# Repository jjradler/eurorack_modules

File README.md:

View this project on [CADLAB.io](https://cadlab.io/project/2451). 

# eurorack_modules

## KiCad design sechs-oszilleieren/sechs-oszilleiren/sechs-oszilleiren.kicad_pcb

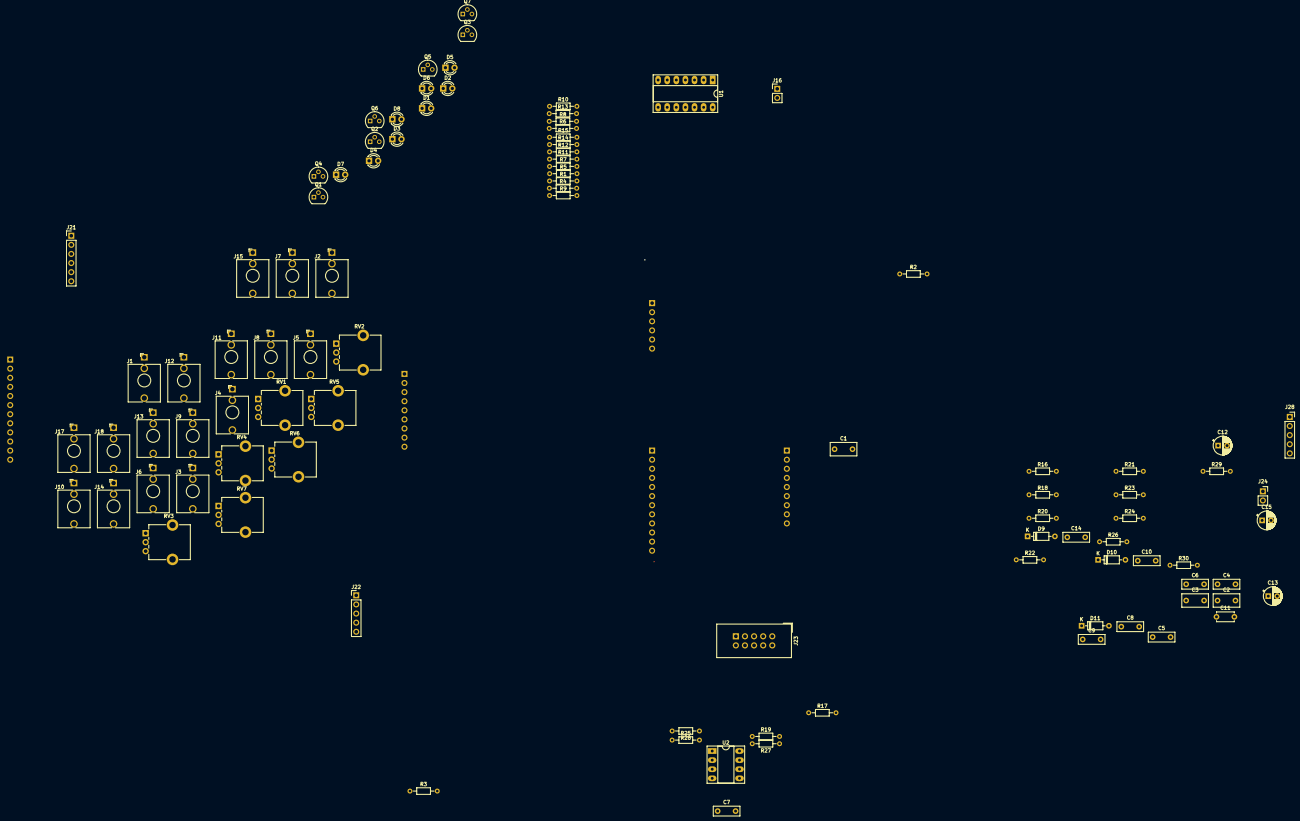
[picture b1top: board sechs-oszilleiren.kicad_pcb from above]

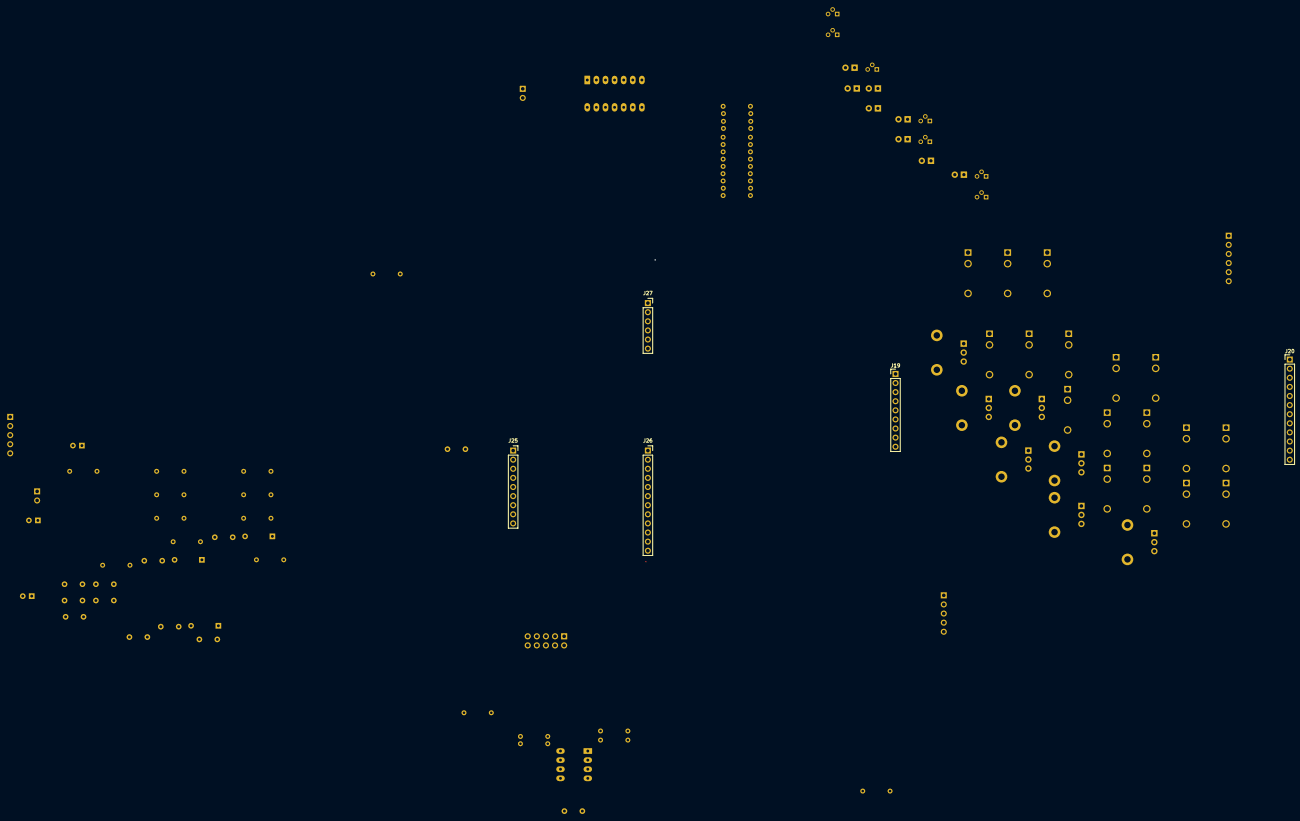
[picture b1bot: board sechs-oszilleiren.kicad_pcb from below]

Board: 2 copper layers, 100 parts (5 on the bottom side), 82 nets.

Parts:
C1, C2, C3: 1.0uF; C_Rect_L7.2mm_W3.5mm_P5.00mm_FKS2_FKP2_MKS2_MKP2
C4, C5, C6, C7, C8, C9: 0.1uF; C_Rect_L7.2mm_W2.5mm_P5.00mm_FKS2_FKP2_MKS2_MKP2
C10: 47pF; C_Rect_L7.2mm_W2.5mm_P5.00mm_FKS2_FKP2_MKS2_MKP2
C11: 27pF; C_Disc_D4.7mm_W2.5mm_P5.00mm
C12, C13, C15: 10uF; CP_Radial_D5.0mm_P2.50mm
C14: 0.01uF; C_Rect_L7.2mm_W2.5mm_P5.00mm_FKS2_FKP2_MKS2_MKP2
D1, D2, D3, D4, D5, D6, D7: R; LED_D3.0mm
D8: Y; LED_D3.0mm
D9, D10, D11: 1N4148; D_DO-35_SOD27_P7.62mm_Horizontal
J1, J2, J3, J4, J5, J6, J7, J8, J9, J10, J11, J12, J13, J14, J15, J17, J18: AudioJack2; Jack_3.5mm_QingPu_WQP-PJ398SM_Vertical_CircularHoles
J16: Conn_01x02_Male; PinHeader_1x02_P2.54mm_Vertical
J19: Conn_01x09_Male; PinHeader_1x09_P2.54mm_Vertical
J20: Conn_01x12_Male; PinHeader_1x12_P2.54mm_Vertical
J21: Conn_01x06_Male; PinHeader_1x06_P2.54mm_Vertical
J22: Conn_01x05_Male; PinHeader_1x05_P2.54mm_Vertical
J23: Conn_IDC_Box_Header_02x05_Top_Bottom; IDC-Header_2x05_Pitch2.54mm_Straight
J24: Conn_01x02_Female; PinSocket_1x02_P2.54mm_Vertical
J25: Conn_01x09_Female; PinSocket_1x09_P2.54mm_Vertical
J26: Conn_01x12_Female; PinSocket_1x12_P2.54mm_Vertical
J27: Conn_01x06_Female; PinSocket_1x06_P2.54mm_Vertical
J28: Conn_01x05_Female; PinSocket_1x05_P2.54mm_Vertical
Q1, Q2, Q3, Q4, Q5, Q6, Q7: 2N3904; TO-92
R1, R2, R3, R7, R8, R9, R14, R28: 47K; R_Axial_DIN0204_L3.6mm_D1.6mm_P7.62mm_Horizontal
R4, R5, R6, R10, R11, R12, R15: 2K; R_Axial_DIN0204_L3.6mm_D1.6mm_P7.62mm_Horizontal
R13: 22K; R_Axial_DIN0204_L3.6mm_D1.6mm_P7.62mm_Horizontal
R16, R17, R18: 1K; R_Axial_DIN0204_L3.6mm_D1.6mm_P7.62mm_Horizontal
R19, R20, R21, R22, R23, R24, R25, R26, R27: 10K; R_Axial_DIN0204_L3.6mm_D1.6mm_P7.62mm_Horizontal
R29, R30: 100R; R_Axial_DIN0204_L3.6mm_D1.6mm_P7.62mm_Horizontal
RV1, RV2, RV3, RV4, RV5, RV6: B100K; Potentiometer_Alpha_RD901F-40-00D_Single_Vertical_CircularH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
RV7: A10K; Potentiometer_Alpha_RD901F-40-00D_Single_Vertical_CircularH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
U1: 40106; DIP-14_W7.62mm_Socket_LongPads
U2: TL072; DIP-8_W7.62mm_Socket_LongPads

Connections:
+12V: C8.1, C9.1, C14.2, C15.1, J16.2, J23.9, J23.10, J24.1, R4.1, R5.1, R6.1, R10.1, R11.1, R12.1, R13.1, R15.1, U1.14, U2.8
/control_board/level_pot_w: J22.4, RV7.2
/control_board/output_indicator: J22.1, R14.2
/control_board/vco_a_cv: J1.T, J19.9
/control_board/vco_a_out: J4.T, J21.6
/control_board/vco_a_pitch_1: J20.12, RV1.1
/control_board/vco_a_pitch_2: R1.2, RV1.2, RV1.3
/control_board/vco_b_cv: J2.T, J19.8
/control_board/vco_b_out: J5.T, J21.5
/control_board/vco_b_pitch_1: J20.11, RV2.1
/control_board/vco_b_pitch_2: R2.2, RV2.2, RV2.3
/control_board/vco_c_cv: J3.T, J19.7
/control_board/vco_c_out: J6.T, J21.4
/control_board/vco_c_pitch_1: J20.10, RV3.1
/control_board/vco_c_pitch_2: R3.2, RV3.2, RV3.3
/control_board/vco_d_cv: J8.T, J19.6
/control_board/vco_d_out: J14.T, J21.3
/control_board/vco_d_pitch_1: J20.9, RV5.1
/control_board/vco_d_pitch_2: R8.2, RV5.2, RV5.3
/control_board/vco_d_sync: J7.T, J19.3
/control_board/vco_e_cv: J10.T, J19.5
/control_board/vco_e_out: J15.T, J21.2
/control_board/vco_e_pitch_1: J20.8, RV6.1
/control_board/vco_e_pitch_2: R9.2, RV6.2, RV6.3
/control_board/vco_e_sync: J9.T, J19.2
/control_board/vco_f_cv: J11.T, J19.4
/control_board/vco_f_out: J13.T, J21.1
/control_board/vco_f_pitch_1: J20.7, RV4.1
/control_board/vco_f_pitch_2: R7.2, RV4.2, RV4.3
/control_board/vco_f_sync: J12.T, J19.1
/voice_board/MIX_A: J26.7, J27.1, R23.1, U1.2
/voice_board/MIX_B: J26.8, J27.2, R22.1, U1.4
/voice_board/MIX_C: J26.9, J27.3, R21.1, U1.6
/voice_board/MIX_D: J26.10, J27.4, R20.1, U1.8
/voice_board/MIX_E: J26.11, J27.5, R19.1, U1.10
/voice_board/MIX_F: J26.12, J27.6, R24.1, U1.12
/voice_board/level_pot_1: C10.1, J28.1, R25.2, R28.1, U2.1
/voice_board/level_pot_w: J28.2, R29.1, R30.1
/voice_board/output_1: C12.2, J28.3
/voice_board/output_2: C13.2, J28.4
/voice_board/output_indicator: J28.5, R28.2
/voice_board/vco_a_cv: C1.1, J25.1, J26.1, U1.1
/voice_board/vco_b_cv: C2.1, J25.2, J26.2, U1.3
/voice_board/vco_c_cv: C3.1, J25.3, J26.3, U1.5
/voice_board/vco_d_cv: C6.1, J25.4, J26.4, R18.1, U1.9
/voice_board/vco_d_sync: D11.2, J25.7
/voice_board/vco_e_cv: C4.1, J25.5, J26.5, R16.1, U1.11
/voice_board/vco_e_sync: D9.2, J25.8
/voice_board/vco_f_cv: C5.1, J25.6, J26.6, R17.1, U1.13
/voice_board/vco_f_sync: D10.2, J25.9
GND: C1.2, C2.2, C3.2, C4.2, C5.2, C6.2, C7.2, C8.2, C9.2, C14.1, C15.2, D1.1, D2.1, D3.1, D4.1, D5.1, D6.1, D7.1, D8.1, J1.S, J2.S, J3.S, J4.S, J5.S, J6.S, J7.S, J8.S, J9.S, J10.S, J11.S, J12.S, J13.S, J14.S, J15.S, J16.1, J17.S, J18.S, J23.3, J23.4, J23.5, J23.6, J23.7, J23.8, J24.2, RV7.3, U1.7, U2.3, U2.5
unnamed: C7.1, U2.4
unnamed: C10.2, R25.1, R26.2, U2.2
unnamed: C11.1, R26.1, R27.2, U2.7
unnamed: C11.2, R19.2, R20.2, R21.2, R22.2, R23.2, R24.2, R27.1, U2.6
unnamed: C12.1, R29.2
unnamed: C13.1, R30.2
unnamed: D1.2, Q1.1
unnamed: D2.2, Q2.1
unnamed: D3.2, Q3.1
unnamed: D4.2, Q4.1
unnamed: D5.2, Q5.1
unnamed: D6.2, Q6.1
unnamed: D7.2, R13.2
unnamed: D8.2, Q7.1
unnamed: D9.1, R16.2
unnamed: D10.1, R17.2
unnamed: D11.1, R18.2
unnamed: Q1.2, R1.1
unnamed: Q1.3, R4.2
unnamed: Q2.2, R2.1
unnamed: Q2.3, R5.2
unnamed: Q3.2, R3.1
unnamed: Q3.3, R6.2
unnamed: Q4.2, R7.1
unnamed: Q4.3, R10.2
unnamed: Q5.2, R8.1
unnamed: Q5.3, R11.2
unnamed: Q6.2, R9.1
unnamed: Q6.3, R12.2
unnamed: Q7.2, R14.1
unnamed: Q7.3, R15.2

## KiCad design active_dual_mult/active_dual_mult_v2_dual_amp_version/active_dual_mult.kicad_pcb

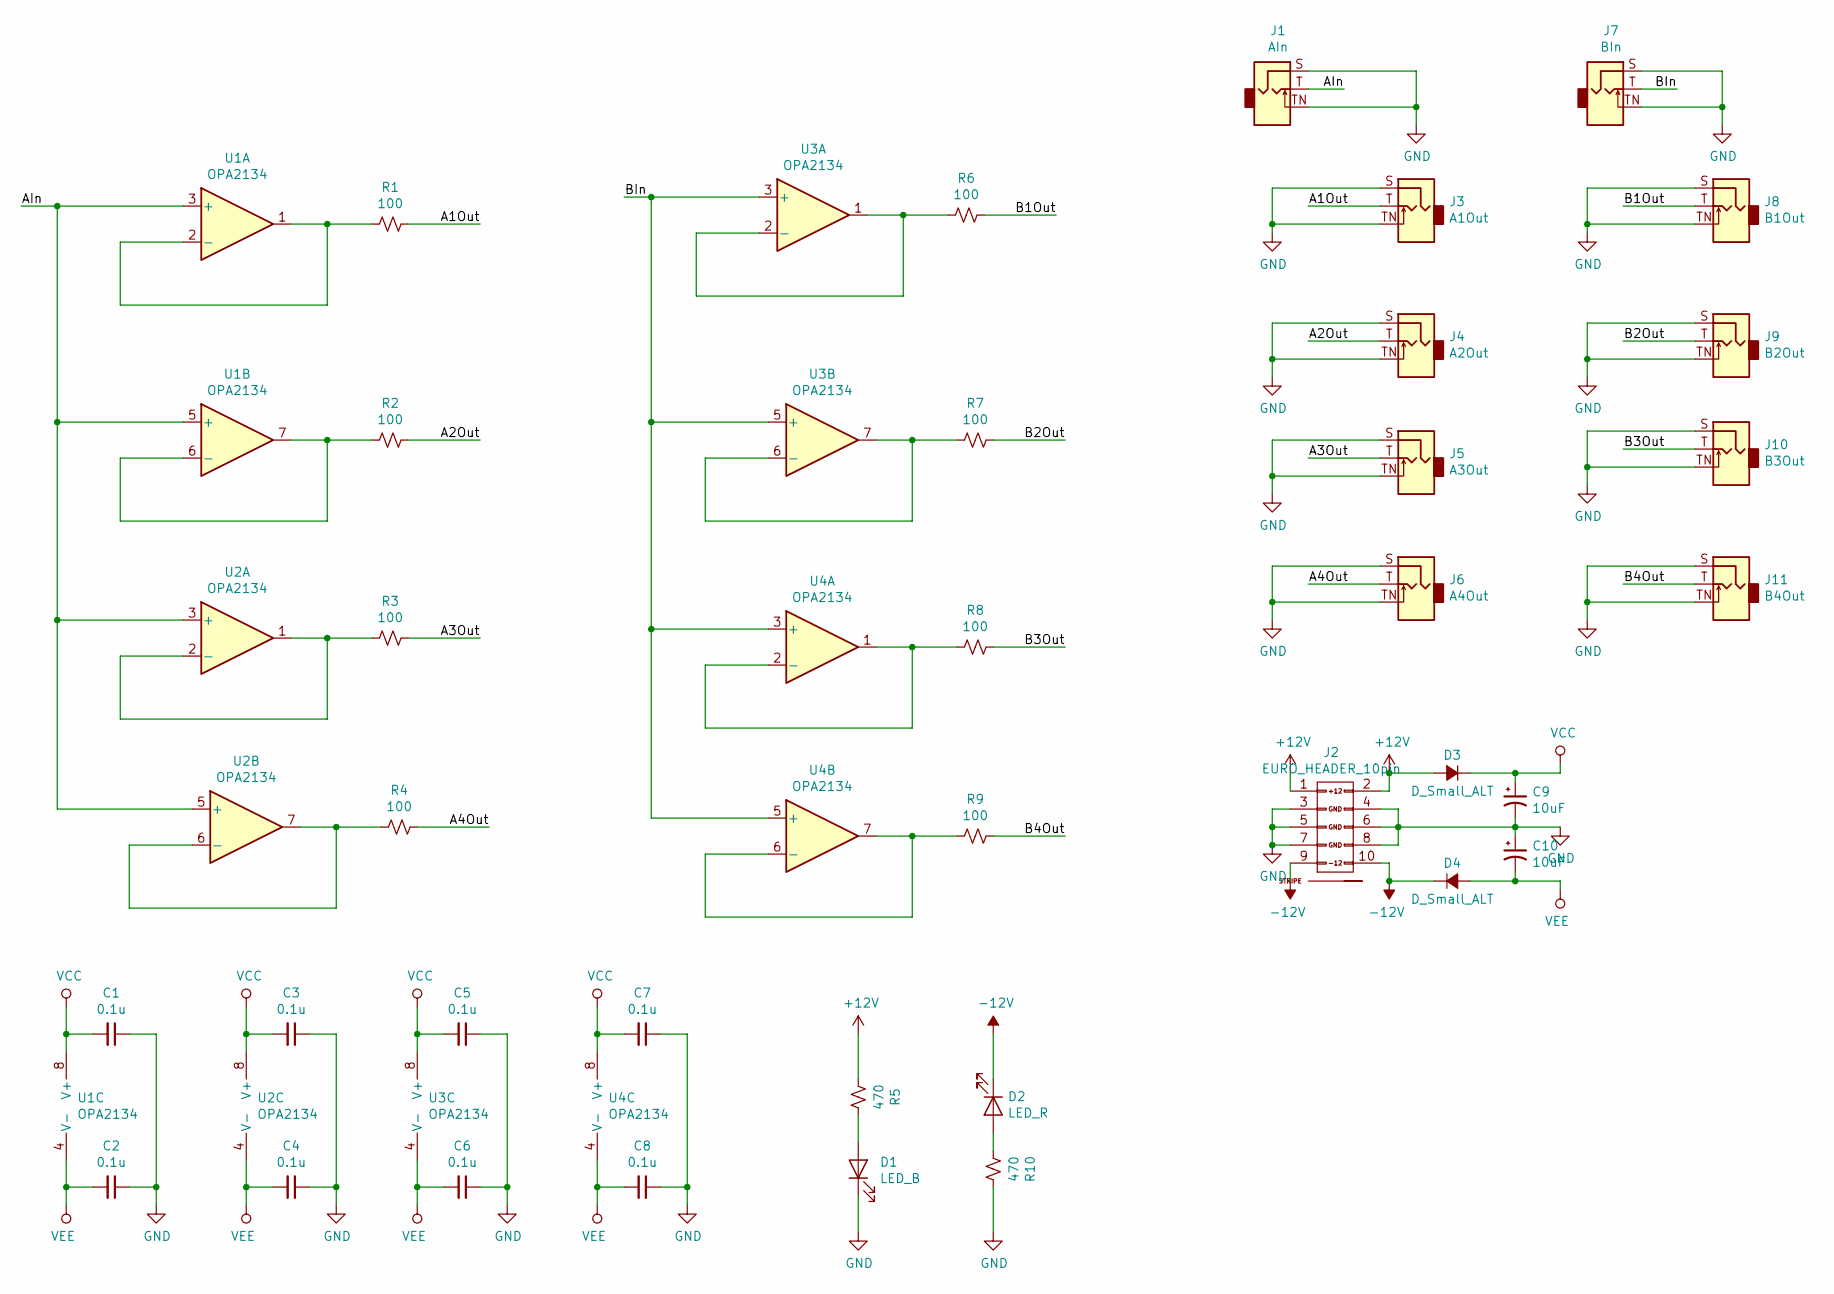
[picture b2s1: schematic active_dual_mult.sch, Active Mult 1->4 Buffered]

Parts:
C1, C2, C3, C4, C5, C6, C7, C8: 0.1u; C_0805
C9, C10: 10uF; C_0805
D1: LED_B; LED_1206_3216Metric_Pad1.42x1.75mm_HandSolder
D2: LED_R; LED_1206_3216Metric_Pad1.42x1.75mm_HandSolder
D3, D4: D_Small_ALT; D_SOD-323_HandSoldering
J1: AIn; Jack_3.5mm_QingPu_WQP-PJ398SM_Vertical_CircularHoles
J2: EURO_HEADER_10pin; Header_2x05_Pitch2.54mm_TH_-12v_Label
J3: A1Out; Jack_3.5mm_QingPu_WQP-PJ398SM_Vertical_CircularHoles
J4: A2Out; Jack_3.5mm_QingPu_WQP-PJ398SM_Vertical_CircularHoles
J5: A3Out; Jack_3.5mm_QingPu_WQP-PJ398SM_Vertical_CircularHoles
J6: A4Out; Jack_3.5mm_QingPu_WQP-PJ398SM_Vertical_CircularHoles
J7: BIn; Jack_3.5mm_QingPu_WQP-PJ398SM_Vertical_CircularHoles
J8: B1Out; Jack_3.5mm_QingPu_WQP-PJ398SM_Vertical_CircularHoles
J9: B2Out; Jack_3.5mm_QingPu_WQP-PJ398SM_Vertical_CircularHoles
J10: B3Out; Jack_3.5mm_QingPu_WQP-PJ398SM_Vertical_CircularHoles
J11: B4Out; Jack_3.5mm_QingPu_WQP-PJ398SM_Vertical_CircularHoles
R1, R2, R3, R4, R6, R7, R8, R9: 100; R_0805_2012Metric_Pad1.15x1.40mm_HandSolder
R5, R10: 470; R_0805_2012Metric_Pad1.15x1.40mm_HandSolder
U1, U2, U3, U4: OPA2134; SOIC-8_5.28x4.9mm_Pitch1.27mm

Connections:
+12V: D3.2 (A), J2.1 (+12V), J2.2 (+12V), R5.2
-12V: D2.1 (K), D4.1 (K), J2.9 (-12V), J2.10 (-12V)
/A1Out: J3.T, R1.1
/A2Out: J4.T, R2.1
/A3Out: J5.T, R3.1
/A4Out: J6.T, R4.1
/AIn: J1.T, U1.3 (+), U1.5 (+), U2.3 (+), U2.5 (+)
/B1Out: J8.T, R6.1
/B2Out: J9.T, R7.1
/B3Out: J10.T, R8.1
/B4Out: J11.T, R9.1
/BIn: J7.T, U3.3 (+), U3.5 (+), U4.3 (+), U4.5 (+)
GND: C1.1, C2.1, C3.1, C4.1, C5.1, C6.1, C7.1, C8.1, C9.2, C10.1, D1.1 (K), J1.S, J1.TN, J2.3 (GND), J2.4 (GND), J2.5 (GND), J2.6 (GND), J2.7 (GND), J2.8 (GND), J3.S, J3.TN, J4.S, J4.TN, J5.S, J5.TN, J6.S, J6.TN, J7.S, J7.TN, J8.S, J8.TN, J9.S, J9.TN, J10.S, J10.TN, J11.S, J11.TN, R10.1
unnamed: D1.2 (A), R5.1
unnamed: D2.2 (A), R10.2
unnamed: R1.2, U1.1, U1.2 (-)
unnamed: R2.2, U1.6 (-), U1.7
unnamed: R3.2, U2.1, U2.2 (-)
unnamed: R4.2, U2.6 (-), U2.7
unnamed: R6.2, U3.1, U3.2 (-)
unnamed: R7.2, U3.6 (-), U3.7
unnamed: R8.2, U4.1, U4.2 (-)
unnamed: R9.2, U4.6 (-), U4.7
VCC: C1.2, C3.2, C5.2, C7.2, C9.1, D3.1 (K), U1.8 (V+), U2.8 (V+), U3.8 (V+), U4.8 (V+)
VEE: C2.2, C4.2, C6.2, C8.2, C10.2, D4.2 (A), U1.4 (V-), U2.4 (V-), U3.4 (V-), U4.4 (V-)

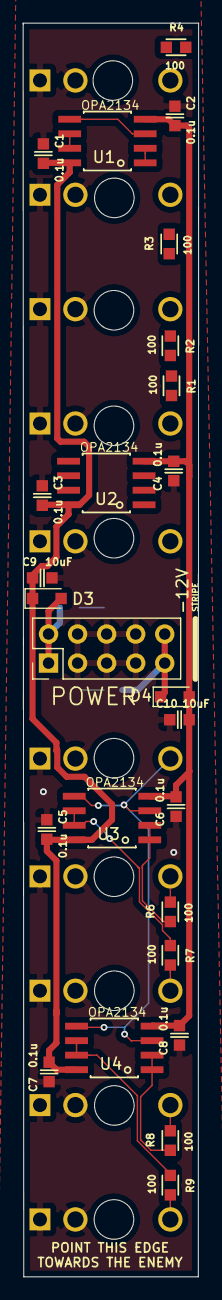
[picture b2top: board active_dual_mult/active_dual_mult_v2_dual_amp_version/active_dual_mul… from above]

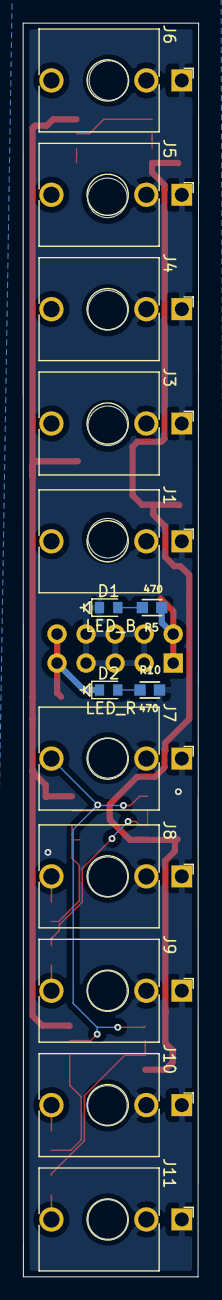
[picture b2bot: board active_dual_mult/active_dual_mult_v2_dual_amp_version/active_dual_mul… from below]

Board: 2 copper layers, 15.3 x 109.6 mm, 39 parts (14 on the bottom side), 25 nets.

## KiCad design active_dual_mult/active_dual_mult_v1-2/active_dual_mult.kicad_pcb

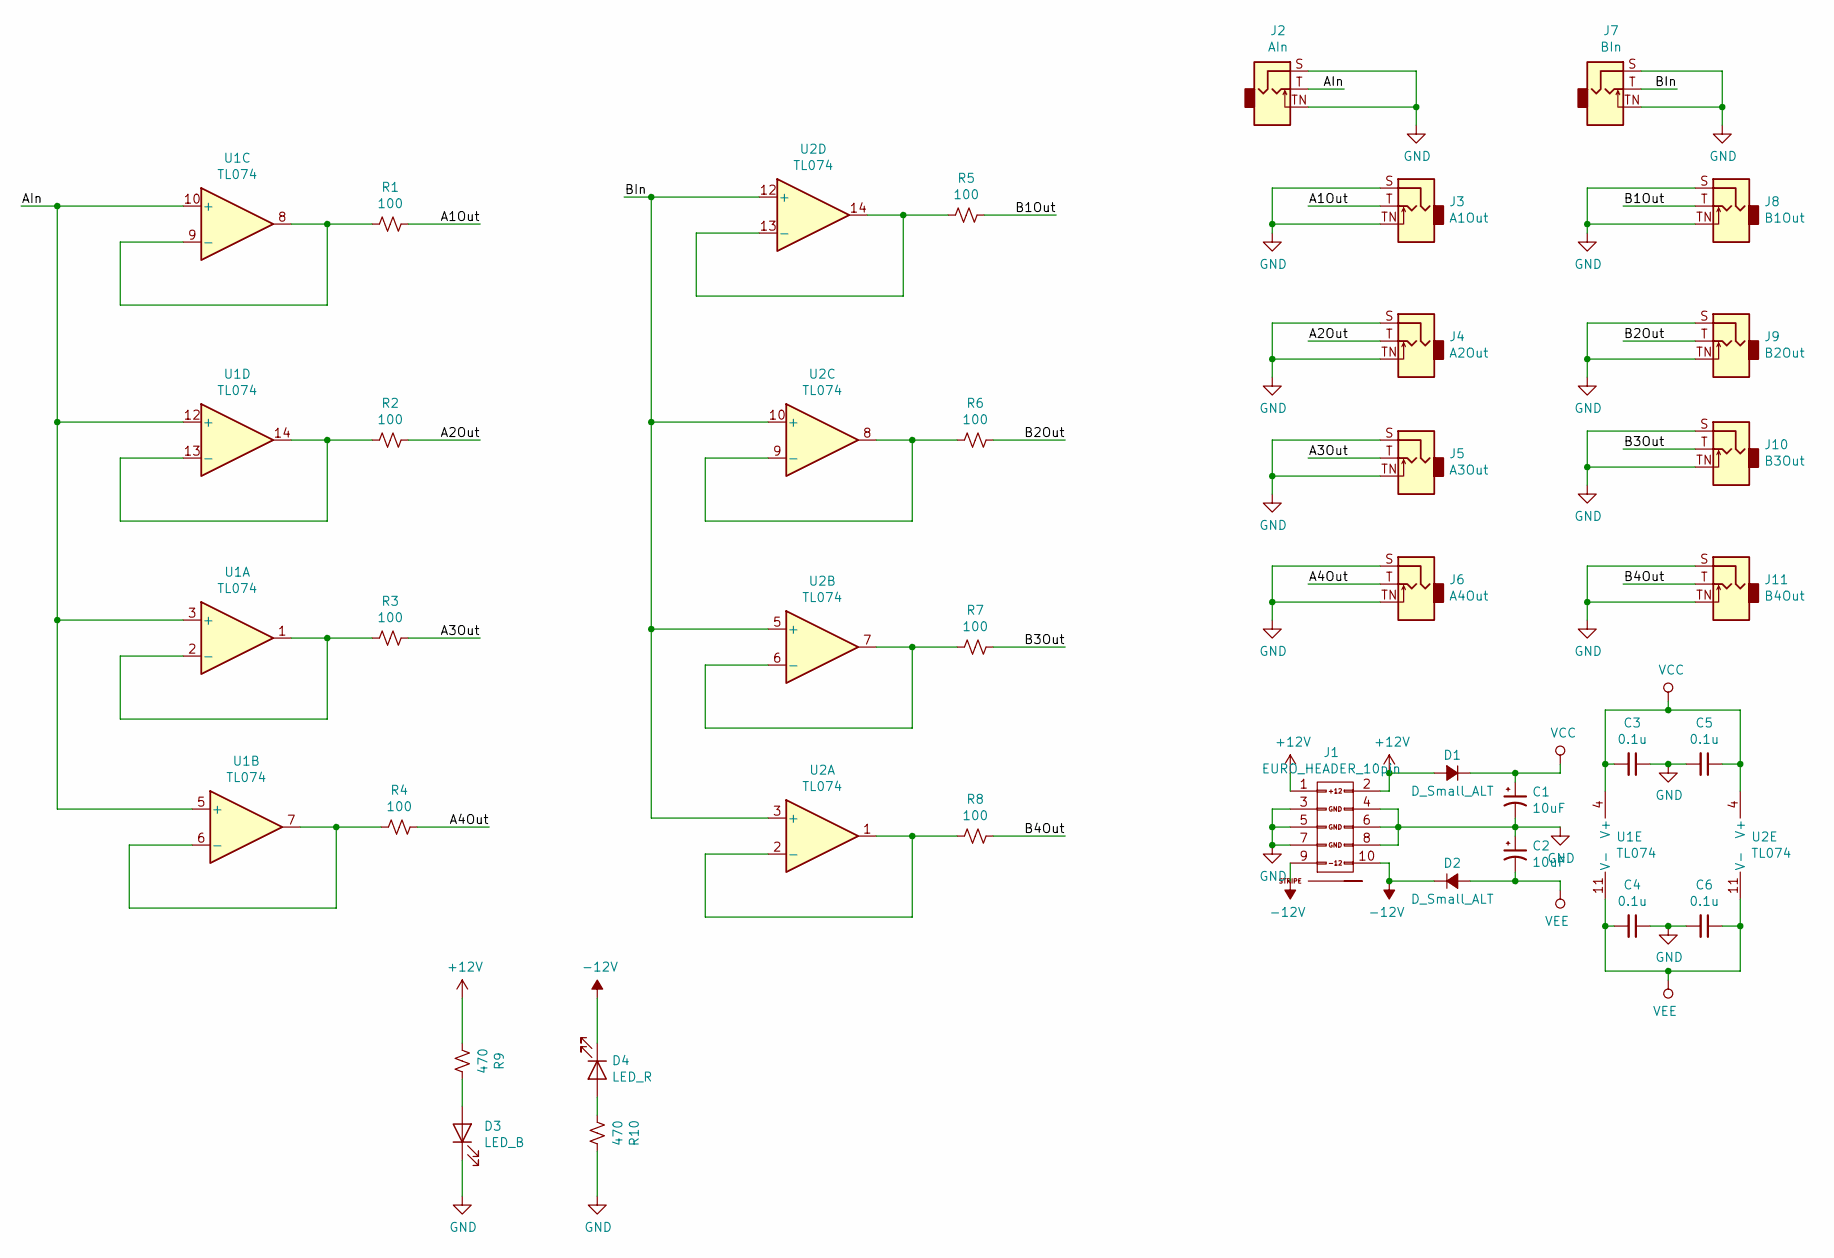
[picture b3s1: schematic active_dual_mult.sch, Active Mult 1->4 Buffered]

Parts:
C1, C2: 10uF; CP_Elec_3x5.4
C3, C4, C5, C6: 0.1u; C_0805
D1, D2: D_Small_ALT; D_SOD-323_HandSoldering
D3: LED_B; LED_1206_3216Metric_Pad1.42x1.75mm_HandSolder
D4: LED_R; LED_1206_3216Metric_Pad1.42x1.75mm_HandSolder
J1: EURO_HEADER_10pin; Header_2x05_Pitch2.54mm_TH_-12v_Label
J2: AIn; Jack_3.5mm_QingPu_WQP-PJ398SM_Vertical_CircularHoles
J3: A1Out; Jack_3.5mm_QingPu_WQP-PJ398SM_Vertical_CircularHoles
J4: A2Out; Jack_3.5mm_QingPu_WQP-PJ398SM_Vertical_CircularHoles
J5: A3Out; Jack_3.5mm_QingPu_WQP-PJ398SM_Vertical_CircularHoles
J6: A4Out; Jack_3.5mm_QingPu_WQP-PJ398SM_Vertical_CircularHoles
J7: BIn; Jack_3.5mm_QingPu_WQP-PJ398SM_Vertical_CircularHoles
J8: B1Out; Jack_3.5mm_QingPu_WQP-PJ398SM_Vertical_CircularHoles
J9: B2Out; Jack_3.5mm_QingPu_WQP-PJ398SM_Vertical_CircularHoles
J10: B3Out; Jack_3.5mm_QingPu_WQP-PJ398SM_Vertical_CircularHoles
J11: B4Out; Jack_3.5mm_QingPu_WQP-PJ398SM_Vertical_CircularHoles
R1, R2, R3, R4, R5, R6, R7, R8: 100; R_0805_2012Metric_Pad1.15x1.40mm_HandSolder
R9, R10: 470; R_0805_2012Metric_Pad1.15x1.40mm_HandSolder
U1, U2: TL074; TSSOP-14_4.4x5mm_P0.65mm

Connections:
+12V: D1.2 (A), J1.1 (+12V), J1.2 (+12V), R9.2
-12V: D2.1 (K), D4.1 (K), J1.9 (-12V), J1.10 (-12V)
/A1Out: J3.T, R1.1
/A2Out: J4.T, R2.1
/A3Out: J5.T, R3.1
/A4Out: J6.T, R4.1
/AIn: J2.T, U1.3 (+), U1.5 (+), U1.10 (+), U1.12 (+)
/B1Out: J8.T, R5.1
/B2Out: J9.T, R6.1
/B3Out: J10.T, R7.1
/B4Out: J11.T, R8.1
/BIn: J7.T, U2.3 (+), U2.5 (+), U2.10 (+), U2.12 (+)
GND: C1.2, C2.1, C3.1, C4.1, C5.2, C6.2, D3.1 (K), J1.3 (GND), J1.4 (GND), J1.5 (GND), J1.6 (GND), J1.7 (GND), J1.8 (GND), J2.S, J2.TN, J3.S, J3.TN, J4.S, J4.TN, J5.S, J5.TN, J6.S, J6.TN, J7.S, J7.TN, J8.S, J8.TN, J9.S, J9.TN, J10.S, J10.TN, J11.S, J11.TN, R10.1
unnamed: D3.2 (A), R9.1
unnamed: D4.2 (A), R10.2
unnamed: R1.2, U1.8, U1.9 (-)
unnamed: R2.2, U1.13 (-), U1.14
unnamed: R3.2, U1.1, U1.2 (-)
unnamed: R4.2, U1.6 (-), U1.7
unnamed: R5.2, U2.13 (-), U2.14
unnamed: R6.2, U2.8, U2.9 (-)
unnamed: R7.2, U2.6 (-), U2.7
unnamed: R8.2, U2.1, U2.2 (-)
VCC: C1.1, C3.2, C5.1, D1.1 (K), U1.4 (V+), U2.4 (V+)
VEE: C2.2, C4.2, C6.1, D2.2 (A), U1.11 (V-), U2.11 (V-)

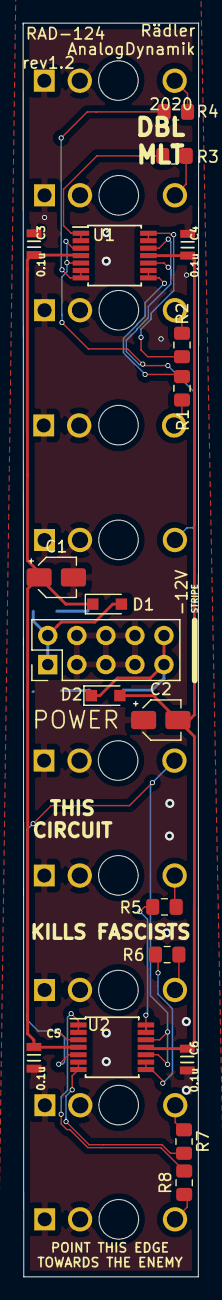
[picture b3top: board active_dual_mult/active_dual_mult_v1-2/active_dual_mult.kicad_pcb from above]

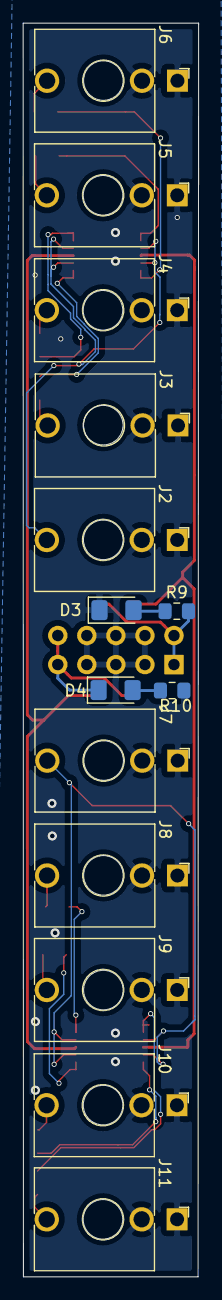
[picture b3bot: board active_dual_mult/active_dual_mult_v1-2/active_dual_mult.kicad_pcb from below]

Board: 2 copper layers, 15.3 x 109.6 mm, 33 parts (14 on the bottom side), 25 nets.

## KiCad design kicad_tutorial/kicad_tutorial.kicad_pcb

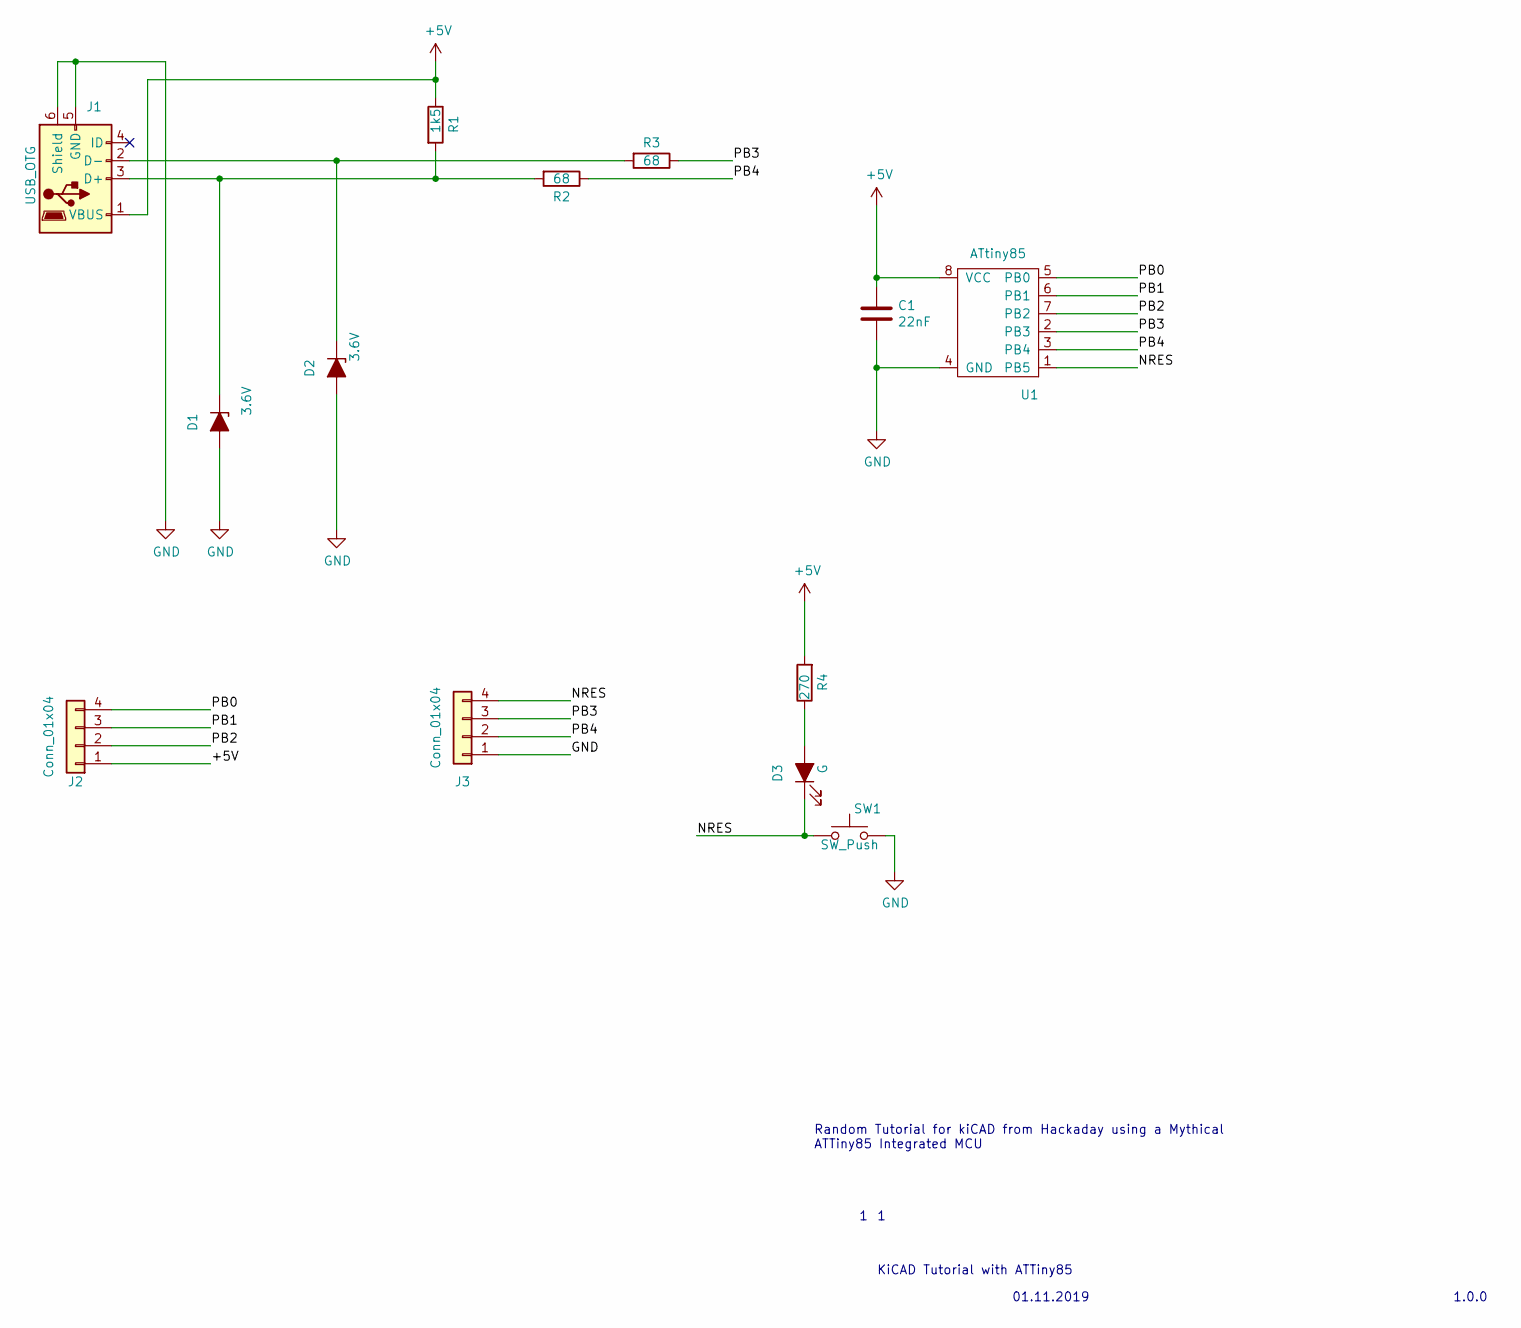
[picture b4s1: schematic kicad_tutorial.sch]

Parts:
C1: 22nF; C_0805_2012Metric
D1, D2: 3.6V; D_0805_2012Metric
D3: G; LED_0805_2012Metric
J1: USB_OTG; USB_Micro-B_Wuerth_629105150521
J2, J3: Conn_01x04; PinHeader_1x04_P1.27mm_Vertical_SMD_Pin1Left
R1: 1k5; R_0805_2012Metric
R2, R3: 68; R_0805_2012Metric
R4: 270; R_0805_2012Metric
SW1: SW_Push; SW_Push_SPST_NO_Alps_SKRK
U1: ATtiny85; TSOT-23-8

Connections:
+5V: C1.1, J1.1 (VBUS), J2.1, R1.1, R4.2, U1.8 (VCC)
/NRES: D3.1 (K), J3.4, SW1.1, U1.1 (PB5)
/PB0: J2.4, U1.5 (PB0)
/PB1: J2.3, U1.6 (PB1)
/PB2: J2.2, U1.7 (PB2)
/PB3: J3.3, R3.1, U1.2 (PB3)
/PB4: J3.2, R2.1, U1.3 (PB4)
GND: C1.2, D1.2 (A), D2.2 (A), J1.5 (GND), J1.6 (Shield), J3.1, SW1.2, U1.4 (GND)
unnamed: D1.1 (K), J1.3 (D+), R1.2, R2.2
unnamed: D2.1 (K), J1.2 (D-), R3.2
unnamed: D3.2 (A), R4.1

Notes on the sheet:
Random Tutorial for kiCAD from Hackaday using a Mythical ATTiny85 Integrated MCU
KiCAD Tutorial with ATTiny85
01.11.2019
1.0.0

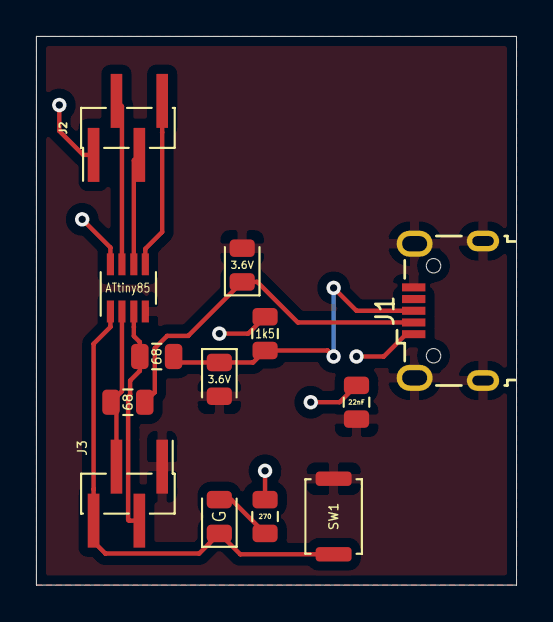
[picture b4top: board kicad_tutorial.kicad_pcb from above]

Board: 2 copper layers, 26.7 x 30.5 mm, 13 parts (0 on the bottom side), 11 nets.

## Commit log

2020-01-07 Added my builds under one eurorack_modules umbrella.
2020-01-07 Added some documentation.
2020-01-07 Removed a conflicting file I didn't need anyway.
2020-02-04 Backlink to CADLAB.io has been added.
2020-02-04 First commit on Eurorack Modules repo.
2020-02-04 added the first segment of the 40106 to the *.sch file.
2020-02-04 Added the remaining segments as well as a mixing output stage and indicator lights.
2020-02-04 Added nearly all parts and wires. Some are being stubborn and will need some revision.
2020-02-05 Totally rerouted the board to make sure all connections are made. It's still an awful mess, so I think board layout needs to be carefully reconsidered if I want to fit it in this form factor...
2020-03-09 I don't remember how this changed, but git tells me it did...
2020-03-12 Started rearranging the components on the boards such that a panel may also be laid out in FR4
2020-03-14 Broke up the schematic into two boards.
2020-03-14 Added board connector pins and reformatted the schematic to account for 2 board design.
2020-03-26 Added a script for configuring the repo for better KiCAD integration.
2020-03-26 Added library for IDC connectors.
2020-03-26 Removed a couple of module directories that I scrapped the designs for.
2020-03-26 Added pins between boards for stacking. Changed all components to THT components.
2020-07-25 Added a number of stages for the attenuverter, vco, and sechs_oszilleieren.
2020-10-05 Reorganized eurorack modules.
2020-10-05 Added a folder for changing the schematic to use dual op amps instead of quad op amps.
2020-10-05 Rewired PCB in version 2 of RAD124 to leverage dual op-amp packages and minimize number of vias for output channels. Changed op amps to OPA2174 SOIC packages to improve unity-gain stability and reduc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
2020-10-09 Added a new revision for RokuXSanXGo
2020-10-09 Rearranged labeling on voice board, simplified output stage and reduced part count. Simplified CD40106 feedback nets.
